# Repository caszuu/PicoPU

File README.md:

# PicoPU

A mecha project focused on building a very simple open-source General Purpose Graphics Processing Unit (GPGPU) using the amazing `rp2350` MCUs as compute cores. The project it self is made of multiple parts: the software drivers, the GPU firmware and the hardware PCB itself.

The project is currently very WIP, more is to come.

Monorepo subprojects:
- `core-firmware/` - PicoPU firmware
	- `common/` - shared firmware utilities
 	- `usbd/` - a protocol generic `tinyusb` device driver
  	- `dvid/` - a simple hstx-based dvi driver
  	- `gcs/` - an arch agnostic software renderer
	- `arch/` - device architecture specific source files
		- `mockbird/` - RPi Pico 2 (mocking bird) arch firmware
- `pdrv/` - a user-space host-side driver written in go
	- `bench/` - an example application using directly `pdrv` apis
- `boards/` - Board design files
	- `images` - used images, #TODO add images of boards
	- `broker` - EasyEDA Std. file for the Broker/Motherboard
	- `shader` - EasyEDA Std. file for the smaller Shader boards
	- `just-V2` - EasyEDA Std. file for the V2 board
	- `pcie` - KiCad project with the "V3" pcie edition

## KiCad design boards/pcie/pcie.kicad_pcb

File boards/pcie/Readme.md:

pcie template from here <3 - https://github.com/lucanastasio/PCIexpress-KiCad/

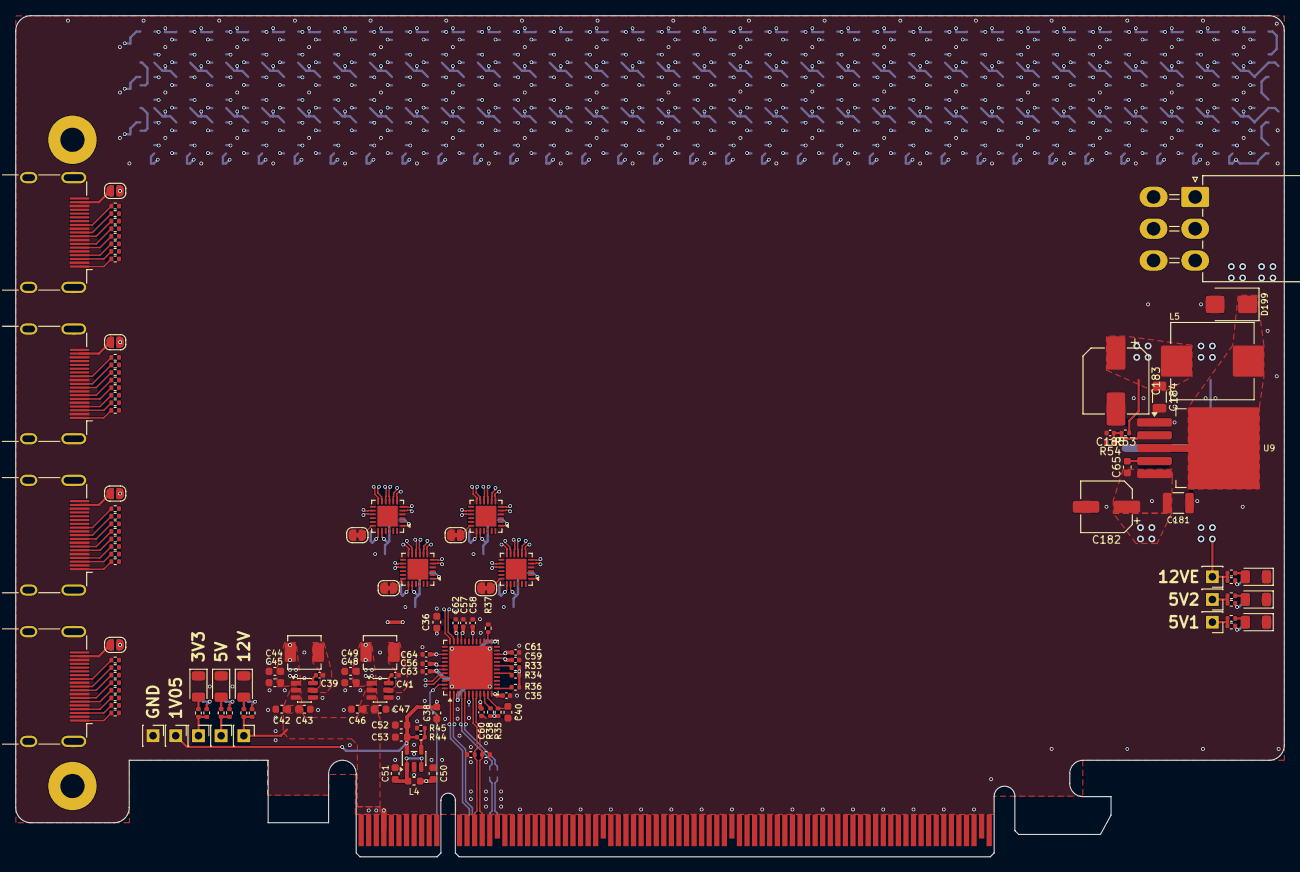
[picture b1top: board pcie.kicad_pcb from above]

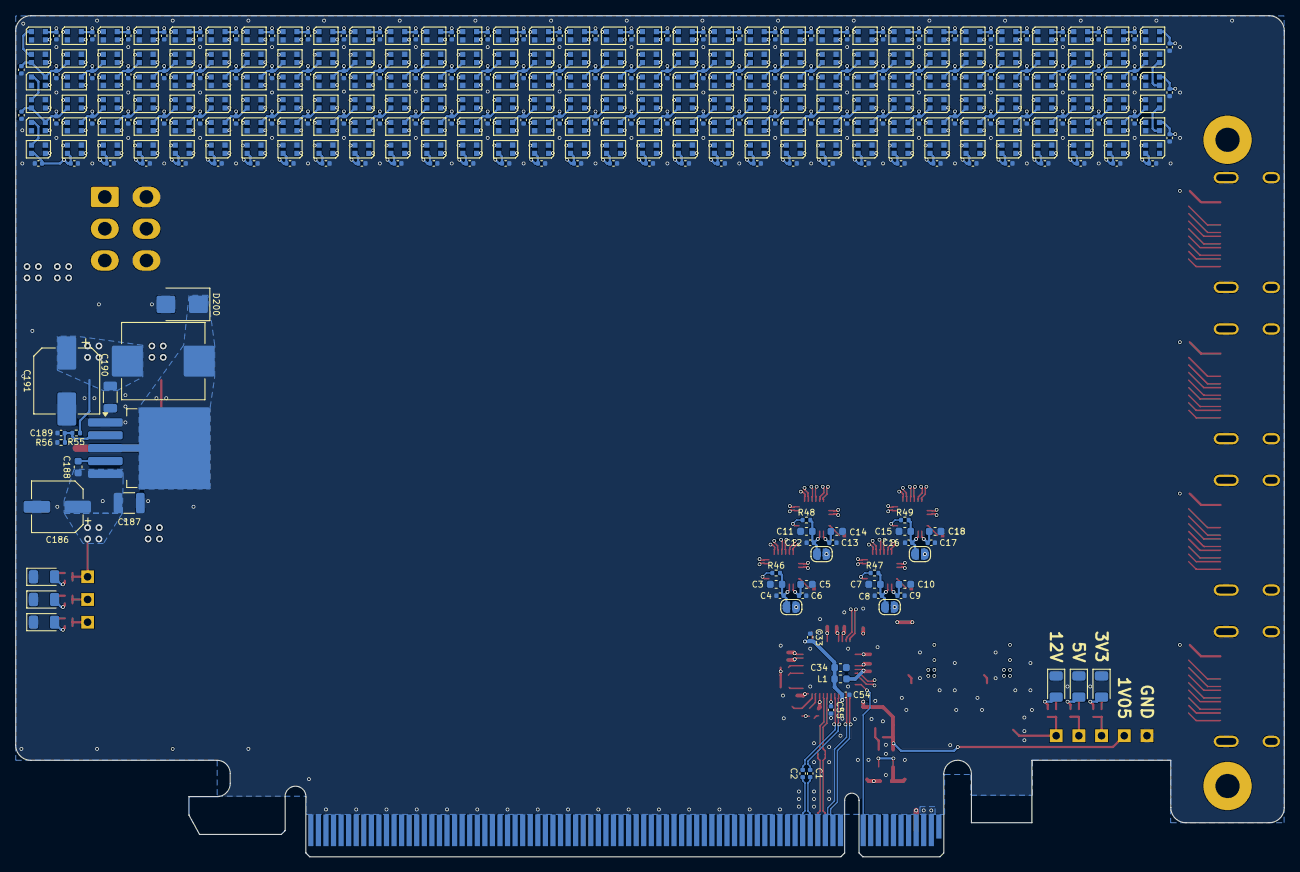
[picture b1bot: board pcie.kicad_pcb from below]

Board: 4 copper layers, 167.6 x 111.2 mm, 504 parts (370 on the bottom side), 295 nets.

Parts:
C1, C2, C4, C6, C8, C9, C12, C13, C16, C17, C19, C20, C21, C22, C23, C24, C25, C26, C27, C28, C29, C30, C31, C32, C33, C35, C37, C39, C41, C54, C55, C56, C57, C58, C59, C60, C61, C62, C63, C64, C66, C67, C68, C69, C70, C71, C72, C73, C74, C75, C76, C77, C78, C79, C80, C81, C82, C83, C84, C85, C86, C87, C88, C89, C90, C91, C92, C93, C94, C95, C96, C97, C98, C99, C100, C101, C102, C103, C104, C105, C106, C107, C108, C109, C110, C111, C112, C113, C114, C115, C116, C117, C118, C119, C120, C121, C122, C123, C124, C125, C126, C127, C128, C129, C130, C131, C132, C133, C134, C135, C136, C137, C138, C139, C140, C141, C142, C143, C144, C145, C146, C147, C148, C149, C150, C151, C152, C153, C154, C155, C156, C157, C158, C159, C160, C161, C162, C163, C164, C165, C166, C167, C168, C169, C170, C171, C172, C173, C174, C175, C176, C177, C178, C179, C180: 100nF; C_0402_1005Metric
C3, C5, C7, C10, C11, C14, C15, C18, C34, C36, C38, C40, C65, C188: 1uF; C_0603_1608Metric
C42, C46, C50, C51, C52: 10uF; C_0603_1608Metric
C43, C44, C45, C47, C48, C49, C53: 22uF; C_0603_1608Metric
C181, C187: 22uF@25V; C_1210_3225Metric
C182, C186: 220uF@25V; CP_Elec_6.3x7.7
C183, C191: 470uF@16V; CP_Elec_8x10.5
C184, C190: 22uF@10V; C_1206_3216Metric
C185, C189: 33nF; C_0402_1005Metric
D1, D4: 12V; LED_1206_3216Metric
D2, D5: 5V; LED_1206_3216Metric
D3, D6: 3V3; LED_1206_3216Metric
D7, D8, D9, D10, D11, D12, D13, D14, D15, D16, D17, D18, D19, D20, D21, D22, D23, D24, D25, D26, D27, D28, D29, D30, D31, D32, D33, D34, D35, D36, D37, D38, D39, D40, D41, D42, D43, D44, D45, D46, D47, D48, D49, D50, D51, D52, D53, D54, D55, D56, D57, D58, D59, D60, D61, D62, D63, D64, D65, D66, D67, D68, D69, D70, D71, D72, D73, D74, D75, D76, D77, D78, D79, D80, D81, D82, D83, D84, D85, D86, D87, D88, D89, D90, D91, D92, D93, D94, D95, D96, D97, D98, D99, D100, D101, D102, D103, D104, D105, D106, D107, D108, D109, D110, D111, D112, D113, D114, D115, D116, D117, D118, D119, D120, D121, D122, D123, D124, D125, D126, D127, D128, D129, D130, D131, D132, D133, D134, D135, D136, D137, D138, D139, D140, D141, D142, D143, D144, D145, D146, D147, D148, D149, D150, D151, D152, D153, D154, D155, D156, D157, D158, D159, D160, D161, D162, D163, D164, D165, D166, D167, D168, D169, D170, D171, D172, D173, D174, D175, D176, D177, D178, D179, D180, D181, D182, D183, D184, D185, D186, D187, D188, D189, D190, D191, D192, D193, D194, D195, D196, D197, D198: LED_45deg; LED_WS2812B-2020_PLCC4_2.0x2.0mm
D199, D200: SS1045-SMB; D_SMB
D201, D202: 12VE; LED_1206_3216Metric
D203, D204: LED_5V1; LED_1206_3216Metric
D205, D206: LED_5V2; LED_1206_3216Metric
H1, H2: MountingHole; MountingHole_3.2mm_M3_Pad
J1: PCIexpress_bracket; PCIexpress_bracket_full
J2: PCIexpress_x16
J3, J13: 12V; PinHeader_1x01_P2.54mm_Vertical
J4, J14, J15: 5V; PinHeader_1x01_P2.54mm_Vertical
J5: 3V3; PinHeader_1x01_P2.54mm_Vertical
J6: 1V0; PinHeader_1x01_P2.54mm_Vertical
J7: GND; PinHeader_1x01_P2.54mm_Vertical
J8, J9, J10, J11: HDMI_A; HDMI_A_Molex_208658-1001_Horizontal
J12: Conn_02x03_Odd_Even; Molex_Mini-Fit_Jr_5569-06A1_2x03_P4.20mm_Horizontal
JP1, JP2, JP3, JP4, JP5, JP8, JP10, JP12: SolderJumper_2_Open; SolderJumper-2_P1.3mm_Open_RoundedPad1.0x1.5mm
JP6, JP7, JP9, JP11: SolderJumper_2_Bridged; SolderJumper-2_P1.3mm_Bridged_RoundedPad1.0x1.5mm
L1, L4: 600Ω@100MHz; L_0603_1608Metric
L2: 4.7uH; L_APV_APH0420
L3: 3.3uH; L_APV_APH0420
L5, L6: 33uH; L_APV_APH1050
R1, R2: 49R9; R_0402_1005Metric
R3, R50, R54, R56, R57, R58: 1k; R_0402_1005Metric
R4, R6, R7, R8, R9, R10, R11, R12, R13, R14, R15, R16, R17, R18, R19, R20, R21, R22, R23, R24, R25, R26, R27, R28, R29, R30, R31, R32, R39, R40, R41, R42, R43, R51, R59, R60, R61, R62: 270; R_0402_1005Metric
R5, R52: 100; R_0402_1005Metric
R33, R34, R36, R38, R45, R46, R47, R48, R49: 10k; R_0402_1005Metric
R35: 100k; R_0402_1005Metric
R37: 12k 1%; R_0402_1005Metric
R44: 9k1; R_0402_1005Metric
R53, R55: 3k; R_0402_1005Metric
U1: AP63203WU; TSOT-23-6
U2: UPD720202K8-701-BAA; QFN-48-1EP_7x7mm_P0.5mm_EP5.7x5.7mm
U3: AP63205WU; TSOT-23-6
U4: TLV75801PDBVR; SOT-23-5
U5, U6, U7, U8: CH334F; QFN-24-1EP_4x4mm_P0.5mm_EP2.7x2.7mm
U9, U10: XL4015; TO-263-5_TabPin3

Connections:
+1V0: C38.1, C52.1, C53.1, C55.1, C56.1, C57.1, C58.1, C59.1, C60.1, C64.1, J6.1 (Pin_1_1), R44.1, U2.6 (VDD10), U2.9 (VDD10), U2.21 (VDD10), U2.30 (VDD10), U2.33 (VDD10), U2.39 (VDD10), U2.42 (VDD10), U4.5 (OUT)
+3V3: C35.1, C36.1, C48.1, C49.1, C50.2, C61.1, C62.1, C63.1, J5.1 (Pin_1_1), JP5.2 (B), JP8.2 (B), JP10.2 (B), JP12.2 (B), L1.1, L3.2, L4.1, R5.1, R33.2, R34.2, R35.1, R36.2, R38.2, R52.1, U1.1 (FB), U2.12 (VDD33), U2.22 (VDD33), U2.34 (VDD33), U2.43 (VDD33)
+5V: C5.1, C6.1, C9.1, C10.1, C13.1, C14.1, C17.1, C18.1, C44.1, C45.1, J4.1 (Pin_1_1), JP1.2 (B), JP2.2 (B), JP3.2 (B), JP4.2 (B), L2.2, R4.1, R51.1, U3.1 (FB), U5.19 (V5), U6.19 (V5), U7.19 (V5), U8.19 (V5)
+12V: C42.1, C43.1, C46.1, C47.1, J2.A2 (+12V), J2.A3 (+12V), J2.B1 (+12V), J2.B2 (+12V), J2.B3 (+12V), J3.1 (Pin_1_1), R3.1, R50.1, U1.2 (EN), U1.3 (IN), U3.2 (EN), U3.3 (IN)
+12VE: C65.1, C181.1, C182.1, C186.1, C187.1, C188.1, J12.1, J12.3, J13.1 (Pin_1_1), R57.1, R58.1, U9.5 (VIN), U10.5 (VIN)
/Hubs/UDUSB1_DN: U5.11 (DM1-), U7.14 (DMU-)
/Hubs/UDUSB1_DP: U5.12 (DP1+), U7.15 (DPU+)
/Hubs/UDUSB2_DN: U6.11 (DM1-), U8.14 (DMU-)
/Hubs/UDUSB2_DP: U6.12 (DP1+), U8.15 (DPU+)
/Hubs/UUSB1_DN: U2.36 (U2DM1), U5.14 (DMU-)
/Hubs/UUSB1_DP: U2.35 (U2DP1), U5.15 (DPU+)
/Hubs/UUSB2_DN: U2.45 (U2DM2), U6.14 (DMU-)
/Hubs/UUSB2_DP: U2.44 (U2DP2), U6.15 (DPU+)
/PER0_N: C2.2, U2.5 (PETXN)
/PER0_P: C1.1, U2.4 (PETXP)
/PET0_N: J2.B15 (PETn0), R1.1, U2.8 (PERXN)
/PET0_P: J2.B14 (PETp0), R2.1, U2.7 (PERXP)
/REFCLK+: J2.A13 (REFCLK+), U2.1 (PECLKP)
/REFCLK-: J2.A14 (REFCLK-), U2.2 (PECLKN)
/_PER0_N: C2.1, J2.A17 (PERn0)
/_PER0_P: C1.2, J2.A16 (PERp0)
/~PERST: J2.A11 (~PERST), U2.47 (~PERST)
GND: C3.2, C4.2, C5.2, C6.2, C7.2, C8.2, C9.2, C10.2, C11.2, C12.2, C13.2, C14.2, C15.2, C16.2, C17.2, C18.2, C19.2, C20.2, C21.2, C22.2, C23.2, C24.2, C25.2, C26.2, C27.2, C28.2, C29.2, C30.2, C31.2, C32.2, C33.1, C34.1, C35.2, C36.2, C37.2, C38.2, C40.2, C42.2, C43.2, C44.2, C45.2, C46.2, C47.2, C48.2, C49.2, C50.1, C51.1, C52.2, C53.2, C54.1, C55.2, C56.2, C57.2, C58.2, C59.2, C60.2, C61.2, C62.2, C63.2, C64.2, C66.2, C67.2, C68.2, C69.2, C70.2, C71.2, C72.2, C73.2, C74.2, C75.2, C76.2, C77.2, C78.2, C79.2, C80.2, C81.2, C82.2, C83.2, C84.2, C85.2, C86.2, C87.2, C88.2, C89.2, C90.2, C91.2, C92.2, C93.2, C94.2, C95.2, C96.2, C97.2, C98.2, C99.2, C100.2, C101.2, C102.2, C103.2, C104.2, C105.2, C106.2, C107.2, C108.2, C109.2, C110.2, C111.2, C112.2, C113.2, C114.2, C115.2, C116.2, C117.2, C118.2, C119.2, C120.2, C121.2, C122.2, C123.2, C124.2, C125.2, C126.2, C127.2, C128.2, C129.2, C130.2, C131.2, C132.2, C133.2, C134.2, C135.2, C136.2, C137.2, C138.2, C139.2, C140.2, C141.2, C142.2, C143.2, C144.2, C145.2, C146.2, C147.2, C148.2, C149.2, C150.2, C151.2, C152.2, C153.2, C154.2, C155.2, C156.2, C157.2, C158.2, C159.2, C160.2, C161.2, C162.2, C163.2, C164.2, C165.2, C166.2, C167.2, C168.2, C169.2, C170.2, C171.2, C172.2, C173.2, C174.2, C175.2, C176.2, C177.2, C178.2, C179.2, C180.2, C181.2, C182.2, C183.2, C184.2, C185.2, C186.2, C187.2, C189.2, C190.2, C191.2, D1.1 (K), D2.1 (K), D3.1 (K), D4.1 (K), D5.1 (K), D6.1 (K), D7.2 (VSS), D8.2 (VSS), D9.2 (VSS), D10.2 (VSS), D11.2 (VSS), D12.2 (VSS), D13.2 (VSS), D14.2 (VSS), D15.2 (VSS), D16.2 (VSS), D17.2 (VSS), D18.2 (VSS), D19.2 (VSS), D20.2 (VSS), D21.2 (VSS), D22.2 (VSS), D23.2 (VSS), D24.2 (VSS), D25.2 (VSS), D26.2 (VSS), D27.2 (VSS), D28.2 (VSS), D29.2 (VSS), D30.2 (VSS), D31.2 (VSS), D32.2 (VSS), D33.2 (VSS), D34.2 (VSS), D35.2 (VSS), D36.2 (VSS), D37.2 (VSS), D38.2 (VSS), D39.2 (VSS), D40.2 (VSS), D41.2 (VSS), D42.2 (VSS), D43.2 (VSS), D44.2 (VSS), D45.2 (VSS), D46.2 (VSS), D47.2 (VSS), D48.2 (VSS), D49.2 (VSS), D50.2 (VSS), D51.2 (VSS), D52.2 (VSS), D53.2 (VSS), D54.2 (VSS), D55.2 (VSS), D56.2 (VSS), D57.2 (VSS), D58.2 (VSS), D59.2 (VSS), D60.2 (VSS), D61.2 (VSS), D62.2 (VSS), D63.2 (VSS), D64.2 (VSS), D65.2 (VSS), D66.2 (VSS), D67.2 (VSS), D68.2 (VSS), D69.2 (VSS), D70.2 (VSS), D71.2 (VSS), D72.2 (VSS), D73.2 (VSS), D74.2 (VSS), D75.2 (VSS), D76.2 (VSS), D77.2 (VSS), D78.2 (VSS), D79.2 (VSS), D80.2 (VSS), D81.2 (VSS), D82.2 (VSS), D83.2 (VSS), D84.2 (VSS), D85.2 (VSS), D86.2 (VSS), D87.2 (VSS), D88.2 (VSS), D89.2 (VSS), D90.2 (VSS), D91.2 (VSS), D92.2 (VSS), D93.2 (VSS), D94.2 (VSS), D95.2 (VSS), D96.2 (VSS), D97.2 (VSS), D98.2 (VSS), D99.2 (VSS), D100.2 (VSS), D101.2 (VSS), D102.2 (VSS), D103.2 (VSS), D104.2 (VSS), D105.2 (VSS), D106.2 (VSS), D107.2 (VSS), D108.2 (VSS), D109.2 (VSS), D110.2 (VSS), D111.2 (VSS), D112.2 (VSS), D113.2 (VSS), D114.2 (VSS), D115.2 (VSS), D116.2 (VSS), D117.2 (VSS), D118.2 (VSS), D119.2 (VSS), D120.2 (VSS), D121.2 (VSS), D122.2 (VSS), D123.2 (VSS), D124.2 (VSS), D125.2 (VSS), D126.2 (VSS), D127.2 (VSS), D128.2 (VSS), D129.2 (VSS), D130.2 (VSS), D131.2 (VSS), D132.2 (VSS), D133.2 (VSS), D134.2 (VSS), D135.2 (VSS), D136.2 (VSS), D137.2 (VSS), D138.2 (VSS), D139.2 (VSS), D140.2 (VSS), D141.2 (VSS), D142.2 (VSS), D143.2 (VSS), D144.2 (VSS), D145.2 (VSS), D146.2 (VSS), D147.2 (VSS), D148.2 (VSS), D149.2 (VSS), D150.2 (VSS), D151.2 (VSS), D152.2 (VSS), D153.2 (VSS), D154.2 (VSS), D155.2 (VSS), D156.2 (VSS), D157.2 (VSS), D158.2 (VSS), D159.2 (VSS), D160.2 (VSS), D161.2 (VSS), D162.2 (VSS), D163.2 (VSS), D164.2 (VSS), D165.2 (VSS), D166.2 (VSS), D167.2 (VSS), D168.2 (VSS), D169.2 (VSS), D170.2 (VSS), D171.2 (VSS), D172.2 (VSS), D173.2 (VSS), D174.2 (VSS), D175.2 (VSS), D176.2 (VSS), D177.2 (VSS), D178.2 (VSS), D179.2 (VSS), D180.2 (VSS), D181.2 (VSS), D182.2 (VSS), D183.2 (VSS), D184.2 (VSS), D185.2 (VSS), D186.2 (VSS), D187.2 (VSS), D188.2 (VSS), D189.2 (VSS), D190.2 (VSS), D191.2 (VSS), D192.2 (VSS), D193.2 (VSS), D194.2 (VSS), D195.2 (VSS), D196.2 (VSS), D197.2 (VSS), D198.2 (VSS), D199.2 (A), D200.2 (A), D201.1 (K), D202.1 (K), D203.1 (K), D204.1 (K), D205.1 (K), D206.1 (K), J2.A4 (GND), J2.A12 (GND), J2.A15 (GND), J2.A18 (GND), J2.A20 (GND), J2.A23 (GND), J2.A24 (GND), J2.A27 (GND), J2.A28 (GND), J2.A31 (GND), J2.A34 (GND), J2.A37 (GND), J2.A38 (GND), J2.A41 (GND), J2.A42 (GND), J2.A45 (GND), J2.A46 (GND), J2.A49 (GND), J2.A51 (GND), J2.A54 (GND), J2.A55 (GND), J2.A58 (GND), J2.A59 (GND), J2.A62 (GND), J2.A63 (GND), J2.A66 (GND), J2.A67 (GND), J2.A70 (GND), J2.A71 (GND), J2.A74 (GND), J2.A75 (GND), J2.A78 (GND), J2.A79 (GND), J2.A82 (GND), J2.B4 (GND), J2.B7 (GND), J2.B13 (GND), J2.B16 (GND), J2.B17 (~PRSNT2), J2.B18 (GND), J2.B21 (GND), J2.B22 (GND), J2.B25 (GND), J2.B26 (GND), J2.B29 (GND), J2.B32 (GND), J2.B35 (GND), J2.B36 (GND), J2.B39 (GND), J2.B40 (GND), J2.B43 (GND), J2.B44 (GND), J2.B47 (GND), J2.B49 (GND), J2.B52 (GND), J2.B53 (GND), J2.B56 (GND), J2.B57 (GND), J2.B60 (GND), J2.B61 (GND), J2.B64 (GND), J2.B65 (GND), J2.B68 (GND), J2.B69 (GND), J2.B72 (GND), J2.B73 (GND), J2.B76 (GND), J2.B77 (GND), J2.B80 (GND), J7.1 (Pin_1_1), J8.2 (D2S), J8.5 (D1S), J8.8 (D0S), J8.11 (CKS), J8.17 (GND), J8.SH, J9.2 (D2S), J9.5 (D1S), J9.8 (D0S), J9.11 (CKS), J9.17 (GND), J9.SH, J10.2 (D2S), J10.5 (D1S), J10.8 (D0S), J10.11 (CKS), J10.17 (GND), J10.SH, J11.2 (D2S), J11.5 (D1S), J11.8 (D0S), J11.11 (CKS), J11.17 (GND), J11.SH, J12.4, J12.6, JP6.1 (A), JP7.1 (A), JP9.1 (A), JP11.1 (A), R1.2, R2.2, R37.2, R45.2, R54.2, R56.2, U1.4 (GND), U2.27 (GND), U2.49 (GND), U3.4 (GND), U4.2 (GND), U5.4 (XI), U5.25 (GND), U6.4 (XI), U6.25 (GND), U7.4 (XI), U7.25 (GND), U8.4 (XI), U8.25 (GND), U9.1 (GND), U10.1 (GND)
LED_5V1: C19.1, C20.1, C21.1, C22.1, C27.1, C28.1, C29.1, C30.1, C31.1, C32.1, C37.1, C66.1, C67.1, C68.1, C69.1, C70.1, C71.1, C72.1, C73.1, C74.1, C75.1, C76.1, C77.1, C78.1, C79.1, C80.1, C81.1, C82.1, C83.1, C84.1, C85.1, C86.1, C87.1, C149.1, C150.1, C151.1, C152.1, C153.1, C154.1, C155.1, C156.1, C157.1, C158.1, C159.1, C160.1, C161.1, C162.1, C163.1, C164.1, C165.1, C166.1, C167.1, C168.1, C169.1, C170.1, C171.1, C172.1, C173.1, C174.1, C175.1, C176.1, C177.1, C178.1, C179.1, C180.1, C190.1, C191.1, D7.4 (VDD), D8.4 (VDD), D9.4 (VDD), D10.4 (VDD), D11.4 (VDD), D12.4 (VDD), D13.4 (VDD), D14.4 (VDD), D15.4 (VDD), D16.4 (VDD), D17.4 (VDD), D18.4 (VDD), D19.4 (VDD), D20.4 (VDD), D21.4 (VDD), D22.4 (VDD), D23.4 (VDD), D24.4 (VDD), D25.4 (VDD), D26.4 (VDD), D27.4 (VDD), D28.4 (VDD), D29.4 (VDD), D30.4 (VDD), D31.4 (VDD), D32.4 (VDD), D33.4 (VDD), D34.4 (VDD), D35.4 (VDD), D36.4 (VDD), D37.4 (VDD), D38.4 (VDD), D39.4 (VDD), D40.4 (VDD), D41.4 (VDD), D42.4 (VDD), D43.4 (VDD), D44.4 (VDD), D45.4 (VDD), D46.4 (VDD), D47.4 (VDD), D48.4 (VDD), D49.4 (VDD), D50.4 (VDD), D51.4 (VDD), D52.4 (VDD), D53.4 (VDD), D54.4 (VDD), D55.4 (VDD), D56.4 (VDD), D57.4 (VDD), D58.4 (VDD), D59.4 (VDD), D60.4 (VDD), D61.4 (VDD), D62.4 (VDD), D63.4 (VDD), D64.4 (VDD), D65.4 (VDD), D66.4 (VDD), D67.4 (VDD), D68.4 (VDD), D69.4 (VDD), D70.4 (VDD), D71.4 (VDD), D72.4 (VDD), D73.4 (VDD), D74.4 (VDD), D75.4 (VDD), D76.4 (VDD), D77.4 (VDD), D78.4 (VDD), D79.4 (VDD), D80.4 (VDD), D81.4 (VDD), D82.4 (VDD), D83.4 (VDD), D84.4 (VDD), D85.4 (VDD), D86.4 (VDD), D87.4 (VDD), D88.4 (VDD), D89.4 (VDD), D90.4 (VDD), D91.4 (VDD), D92.4 (VDD), D93.4 (VDD), D94.4 (VDD), D95.4 (VDD), D96.4 (VDD), D97.4 (VDD), D98.4 (VDD), D99.4 (VDD), D100.4 (VDD), D101.4 (VDD), D102.4 (VDD), J14.1 (Pin_1_1), L6.2, R55.1, R59.1, R60.1
LED_5V2: C23.1, C24.1, C25.1, C26.1, C88.1, C89.1, C90.1, C91.1, C92.1, C93.1, C94.1, C95.1, C96.1, C97.1, C98.1, C99.1, C100.1, C101.1, C102.1, C103.1, C104.1, C105.1, C106.1, C107.1, C108.1, C109.1, C110.1, C111.1, C112.1, C113.1, C114.1, C115.1, C116.1, C117.1, C118.1, C119.1, C120.1, C121.1, C122.1, C123.1, C124.1, C125.1, C126.1, C127.1, C128.1, C129.1, C130.1, C131.1, C132.1, C133.1, C134.1, C135.1, C136.1, C137.1, C138.1, C139.1, C140.1, C141.1, C142.1, C143.1, C144.1, C145.1, C146.1, C147.1, C148.1, C183.1, C184.1, D103.4 (VDD), D104.4 (VDD), D105.4 (VDD), D106.4 (VDD), D107.4 (VDD), D108.4 (VDD), D109.4 (VDD), D110.4 (VDD), D111.4 (VDD), D112.4 (VDD), D113.4 (VDD), D114.4 (VDD), D115.4 (VDD), D116.4 (VDD), D117.4 (VDD), D118.4 (VDD), D119.4 (VDD), D120.4 (VDD), D121.4 (VDD), D122.4 (VDD), D123.4 (VDD), D124.4 (VDD), D125.4 (VDD), D126.4 (VDD), D127.4 (VDD), D128.4 (VDD), D129.4 (VDD), D130.4 (VDD), D131.4 (VDD), D132.4 (VDD), D133.4 (VDD), D134.4 (VDD), D135.4 (VDD), D136.4 (VDD), D137.4 (VDD), D138.4 (VDD), D139.4 (VDD), D140.4 (VDD), D141.4 (VDD), D142.4 (VDD), D143.4 (VDD), D144.4 (VDD), D145.4 (VDD), D146.4 (VDD), D147.4 (VDD), D148.4 (VDD), D149.4 (VDD), D150.4 (VDD), D151.4 (VDD), D152.4 (VDD), D153.4 (VDD), D154.4 (VDD), D155.4 (VDD), D156.4 (VDD), D157.4 (VDD), D158.4 (VDD), D159.4 (VDD), D160.4 (VDD), D161.4 (VDD), D162.4 (VDD), D163.4 (VDD), D164.4 (VDD), D165.4 (VDD), D166.4 (VDD), D167.4 (VDD), D168.4 (VDD), D169.4 (VDD), D170.4 (VDD), D171.4 (VDD), D172.4 (VDD), D173.4 (VDD), D174.4 (VDD), D175.4 (VDD), D176.4 (VDD), D177.4 (VDD), D178.4 (VDD), D179.4 (VDD), D180.4 (VDD), D181.4 (VDD), D182.4 (VDD), D183.4 (VDD), D184.4 (VDD), D185.4 (VDD), D186.4 (VDD), D187.4 (VDD), D188.4 (VDD), D189.4 (VDD), D190.4 (VDD), D191.4 (VDD), D192.4 (VDD), D193.4 (VDD), D194.4 (VDD), D195.4 (VDD), D196.4 (VDD), D197.4 (VDD), D198.4 (VDD), J15.1 (Pin_1_1), L5.2, R53.1, R61.1, R62.1
unnamed: C33.2, C34.2, C54.2, L1.2, U2.3 (AVDD33), U2.25 (AVDD33)
unnamed: D1.2 (A), R3.2
unnamed: D2.2 (A), R4.2
unnamed: D3.2 (A), R5.2
unnamed: D4.2 (A), R50.2
unnamed: D5.2 (A), R51.2
unnamed: D6.2 (A), R52.2
unnamed: D7.1 (DOUT), D8.3 (DIN)
unnamed: D8.1 (DOUT), D9.3 (DIN)
unnamed: D9.1 (DOUT), D10.3 (DIN)
unnamed: D10.1 (DOUT), D11.3 (DIN)
unnamed: D11.1 (DOUT), D12.3 (DIN)
unnamed: D12.1 (DOUT), D13.3 (DIN)
unnamed: D13.1 (DOUT), D14.3 (DIN)
unnamed: D14.1 (DOUT), D15.3 (DIN)
unnamed: D15.1 (DOUT), D16.3 (DIN)
unnamed: D16.1 (DOUT), D17.3 (DIN)
unnamed: D17.1 (DOUT), D18.3 (DIN)
unnamed: D18.1 (DOUT), D19.3 (DIN)
unnamed: D19.1 (DOUT), D20.3 (DIN)
unnamed: D20.1 (DOUT), D21.3 (DIN)
unnamed: D21.1 (DOUT), D22.3 (DIN)
unnamed: D22.1 (DOUT), D23.3 (DIN)
unnamed: D23.1 (DOUT), D24.3 (DIN)
unnamed: D24.1 (DOUT), D25.3 (DIN)
unnamed: D25.1 (DOUT), D26.3 (DIN)
unnamed: D26.1 (DOUT), D27.3 (DIN)
unnamed: D27.1 (DOUT), D28.3 (DIN)
unnamed: D28.1 (DOUT), D29.3 (DIN)
unnamed: D29.1 (DOUT), D30.3 (DIN)
unnamed: D30.1 (DOUT), D31.3 (DIN)
unnamed: D31.1 (DOUT), D32.3 (DIN)
unnamed: D32.1 (DOUT), D33.3 (DIN)
unnamed: D33.1 (DOUT), D34.3 (DIN)
unnamed: D34.1 (DOUT), D35.3 (DIN)
unnamed: D35.1 (DOUT), D36.3 (DIN)
unnamed: D36.1 (DOUT), D37.3 (DIN)
unnamed: D37.1 (DOUT), D38.3 (DIN)
unnamed: D38.1 (DOUT), D39.3 (DIN)
unnamed: D39.1 (DOUT), D40.3 (DIN)
unnamed: D40.1 (DOUT), D41.3 (DIN)
unnamed: D41.1 (DOUT), D42.3 (DIN)
unnamed: D42.1 (DOUT), D43.3 (DIN)
unnamed: D43.1 (DOUT), D44.3 (DIN)
unnamed: D44.1 (DOUT), D45.3 (DIN)
unnamed: D45.1 (DOUT), D46.3 (DIN)
unnamed: D46.1 (DOUT), D47.3 (DIN)
unnamed: D47.1 (DOUT), D48.3 (DIN)
unnamed: D48.1 (DOUT), D49.3 (DIN)
unnamed: D49.1 (DOUT), D50.3 (DIN)
unnamed: D50.1 (DOUT), D51.3 (DIN)
unnamed: D51.1 (DOUT), D52.3 (DIN)
unnamed: D52.1 (DOUT), D53.3 (DIN)
unnamed: D53.1 (DOUT), D54.3 (DIN)
unnamed: D54.1 (DOUT), D55.3 (DIN)
unnamed: D55.1 (DOUT), D56.3 (DIN)
unnamed: D56.1 (DOUT), D57.3 (DIN)
unnamed: D57.1 (DOUT), D58.3 (DIN)
unnamed: D58.1 (DOUT), D59.3 (DIN)
unnamed: D59.1 (DOUT), D60.3 (DIN)
unnamed: D60.1 (DOUT), D61.3 (DIN)
unnamed: D61.1 (DOUT), D62.3 (DIN)
unnamed: D62.1 (DOUT), D63.3 (DIN)
unnamed: D63.1 (DOUT), D64.3 (DIN)
unnamed: D64.1 (DOUT), D65.3 (DIN)
unnamed: D65.1 (DOUT), D66.3 (DIN)
unnamed: D66.1 (DOUT), D67.3 (DIN)
unnamed: D67.1 (DOUT), D68.3 (DIN)
unnamed: D68.1 (DOUT), D69.3 (DIN)
unnamed: D69.1 (DOUT), D70.3 (DIN)
unnamed: D70.1 (DOUT), D71.3 (DIN)
unnamed: D71.1 (DOUT), D72.3 (DIN)
unnamed: D72.1 (DOUT), D73.3 (DIN)
unnamed: D73.1 (DOUT), D74.3 (DIN)
unnamed: D74.1 (DOUT), D75.3 (DIN)
unnamed: D75.1 (DOUT), D76.3 (DIN)
unnamed: D76.1 (DOUT), D77.3 (DIN)
unnamed: D77.1 (DOUT), D78.3 (DIN)
unnamed: D78.1 (DOUT), D79.3 (DIN)
unnamed: D79.1 (DOUT), D80.3 (DIN)
unnamed: D80.1 (DOUT), D81.3 (DIN)
unnamed: D81.1 (DOUT), D82.3 (DIN)
unnamed: D82.1 (DOUT), D83.3 (DIN)
unnamed: D83.1 (DOUT), D84.3 (DIN)
unnamed: D84.1 (DOUT), D85.3 (DIN)
unnamed: D85.1 (DOUT), D86.3 (DIN)
unnamed: D86.1 (DOUT), D87.3 (DIN)
unnamed: D87.1 (DOUT), D88.3 (DIN)
unnamed: D88.1 (DOUT), D89.3 (DIN)
unnamed: D89.1 (DOUT), D90.3 (DIN)
unnamed: D90.1 (DOUT), D91.3 (DIN)
unnamed: D91.1 (DOUT), D92.3 (DIN)
unnamed: D92.1 (DOUT), D93.3 (DIN)
unnamed: D93.1 (DOUT), D94.3 (DIN)
unnamed: D94.1 (DOUT), D95.3 (DIN)
unnamed: D95.1 (DOUT), D96.3 (DIN)
unnamed: D96.1 (DOUT), D97.3 (DIN)
unnamed: D97.1 (DOUT), D98.3 (DIN)
unnamed: D98.1 (DOUT), D99.3 (DIN)
unnamed: D99.1 (DOUT), D100.3 (DIN)
unnamed: D100.1 (DOUT), D101.3 (DIN)
unnamed: D101.1 (DOUT), D102.3 (DIN)
unnamed: D102.1 (DOUT), D103.3 (DIN)
unnamed: D103.1 (DOUT), D104.3 (DIN)
unnamed: D104.1 (DOUT), D105.3 (DIN)
unnamed: D105.1 (DOUT), D106.3 (DIN)
unnamed: D106.1 (DOUT), D107.3 (DIN)
unnamed: D107.1 (DOUT), D108.3 (DIN)
unnamed: D108.1 (DOUT), D109.3 (DIN)
unnamed: D109.1 (DOUT), D110.3 (DIN)
unnamed: D110.1 (DOUT), D111.3 (DIN)
unnamed: D111.1 (DOUT), D112.3 (DIN)
unnamed: D112.1 (DOUT), D113.3 (DIN)
unnamed: D113.1 (DOUT), D114.3 (DIN)
unnamed: D114.1 (DOUT), D115.3 (DIN)
unnamed: D115.1 (DOUT), D116.3 (DIN)
unnamed: D116.1 (DOUT), D117.3 (DIN)
unnamed: D117.1 (DOUT), D118.3 (DIN)
unnamed: D118.1 (DOUT), D119.3 (DIN)
unnamed: D119.1 (DOUT), D120.3 (DIN)
unnamed: D120.1 (DOUT), D121.3 (DIN)
unnamed: D121.1 (DOUT), D122.3 (DIN)
unnamed: D122.1 (DOUT), D123.3 (DIN)
unnamed: D123.1 (DOUT), D124.3 (DIN)
unnamed: D124.1 (DOUT), D125.3 (DIN)
unnamed: D125.1 (DOUT), D126.3 (DIN)
unnamed: D126.1 (DOUT), D127.3 (DIN)
unnamed: D127.1 (DOUT), D128.3 (DIN)
unnamed: D128.1 (DOUT), D129.3 (DIN)
unnamed: D129.1 (DOUT), D130.3 (DIN)
unnamed: D130.1 (DOUT), D131.3 (DIN)
unnamed: D131.1 (DOUT), D132.3 (DIN)
unnamed: D132.1 (DOUT), D133.3 (DIN)
unnamed: D133.1 (DOUT), D134.3 (DIN)
unnamed: D134.1 (DOUT), D135.3 (DIN)
unnamed: D135.1 (DOUT), D136.3 (DIN)
unnamed: D136.1 (DOUT), D137.3 (DIN)
unnamed: D137.1 (DOUT), D138.3 (DIN)
unnamed: D138.1 (DOUT), D139.3 (DIN)
unnamed: D139.1 (DOUT), D140.3 (DIN)
unnamed: D140.1 (DOUT), D141.3 (DIN)
unnamed: D141.1 (DOUT), D142.3 (DIN)
unnamed: D142.1 (DOUT), D143.3 (DIN)
unnamed: D143.1 (DOUT), D144.3 (DIN)
unnamed: D144.1 (DOUT), D145.3 (DIN)
unnamed: D145.1 (DOUT), D146.3 (DIN)
unnamed: D146.1 (DOUT), D147.3 (DIN)
unnamed: D147.1 (DOUT), D148.3 (DIN)
unnamed: D148.1 (DOUT), D149.3 (DIN)
unnamed: D149.1 (DOUT), D150.3 (DIN)
unnamed: D150.1 (DOUT), D151.3 (DIN)
unnamed: D151.1 (DOUT), D152.3 (DIN)
unnamed: D152.1 (DOUT), D153.3 (DIN)
unnamed: D153.1 (DOUT), D154.3 (DIN)
unnamed: D154.1 (DOUT), D155.3 (DIN)
unnamed: D155.1 (DOUT), D156.3 (DIN)
unnamed: D156.1 (DOUT), D157.3 (DIN)
unnamed: D157.1 (DOUT), D158.3 (DIN)
unnamed: D158.1 (DOUT), D159.3 (DIN)
unnamed: D159.1 (DOUT), D160.3 (DIN)
unnamed: D160.1 (DOUT), D161.3 (DIN)
unnamed: D161.1 (DOUT), D162.3 (DIN)
unnamed: D162.1 (DOUT), D163.3 (DIN)
unnamed: D163.1 (DOUT), D164.3 (DIN)
unnamed: D164.1 (DOUT), D165.3 (DIN)
unnamed: D165.1 (DOUT), D166.3 (DIN)
unnamed: D166.1 (DOUT), D167.3 (DIN)
unnamed: D167.1 (DOUT), D168.3 (DIN)
unnamed: D168.1 (DOUT), D169.3 (DIN)
unnamed: D169.1 (DOUT), D170.3 (DIN)
unnamed: D170.1 (DOUT), D171.3 (DIN)
unnamed: D171.1 (DOUT), D172.3 (DIN)
unnamed: D172.1 (DOUT), D173.3 (DIN)
unnamed: D173.1 (DOUT), D174.3 (DIN)
unnamed: D174.1 (DOUT), D175.3 (DIN)
unnamed: D175.1 (DOUT), D176.3 (DIN)
unnamed: D176.1 (DOUT), D177.3 (DIN)
unnamed: D177.1 (DOUT), D178.3 (DIN)
unnamed: D178.1 (DOUT), D179.3 (DIN)
unnamed: D179.1 (DOUT), D180.3 (DIN)
unnamed: D180.1 (DOUT), D181.3 (DIN)
unnamed: D181.1 (DOUT), D182.3 (DIN)
unnamed: D182.1 (DOUT), D183.3 (DIN)
unnamed: D183.1 (DOUT), D184.3 (DIN)
unnamed: D184.1 (DOUT), D185.3 (DIN)
unnamed: D185.1 (DOUT), D186.3 (DIN)
unnamed: D186.1 (DOUT), D187.3 (DIN)
unnamed: D187.1 (DOUT), D188.3 (DIN)
unnamed: D188.1 (DOUT), D189.3 (DIN)
unnamed: D189.1 (DOUT), D190.3 (DIN)
unnamed: D190.1 (DOUT), D191.3 (DIN)
unnamed: D191.1 (DOUT), D192.3 (DIN)
unnamed: D192.1 (DOUT), D193.3 (DIN)
unnamed: D193.1 (DOUT), D194.3 (DIN)
unnamed: D194.1 (DOUT), D195.3 (DIN)
unnamed: D195.1 (DOUT), D196.3 (DIN)
unnamed: D196.1 (DOUT), D197.3 (DIN)
unnamed: D197.1 (DOUT), D198.3 (DIN)
unnamed: D199.1 (K), L5.1, U9.3 (SW)
unnamed: D200.1 (K), L6.1, U10.3 (SW)
unnamed: D201.2 (A), R57.2
unnamed: D202.2 (A), R58.2
unnamed: D203.2 (A), R59.2
unnamed: D204.2 (A), R60.2
unnamed: D205.2 (A), R61.2
unnamed: D206.2 (A), R62.2
unnamed: J8.18 (+5V), JP1.1 (A)
unnamed: J8.12 (CKN), R13.2
unnamed: J8.10 (CKP), R12.2
unnamed: J8.9 (D0N), R11.2
unnamed: J8.7 (D0P), R10.2
unnamed: J8.6 (D1N), R9.2
unnamed: J8.4 (D1P), R8.2
unnamed: J8.3 (D2N), R7.2
unnamed: J8.1 (D2P), R6.2
unnamed: J9.18 (+5V), JP2.1 (A)
unnamed: J9.10 (CK+), R20.2
unnamed: J9.12 (CK-), R21.2
unnamed: J9.7 (D0+), R18.2
unnamed: J9.9 (D0-), R19.2
unnamed: J9.4 (D1+), R16.2
unnamed: J9.6 (D1-), R17.2
unnamed: J9.1 (D2+), R14.2
unnamed: J9.3 (D2-), R15.2
unnamed: J10.18 (+5V), JP3.1 (A)
unnamed: J10.10 (CK+), R28.2
unnamed: J10.12 (CK-), R29.2
unnamed: J10.7 (D0+), R26.2
unnamed: J10.9 (D0-), R27.2
unnamed: J10.4 (D1+), R24.2
unnamed: J10.6 (D1-), R25.2
unnamed: J10.1 (D2+), R22.2
unnamed: J10.3 (D2-), R23.2
unnamed: J11.18 (+5V), JP4.1 (A)
unnamed: J11.10 (CK+), R42.2
unnamed: J11.12 (CK-), R43.2
unnamed: J11.7 (D0+), R40.2
unnamed: J11.9 (D0-), R41.2
unnamed: J11.4 (D1+), R32.2
unnamed: J11.6 (D1-), R39.2
unnamed: J11.1 (D2+), R30.2
unnamed: J11.3 (D2-), R31.2
unnamed: C3.1, C4.1, JP5.1 (A), R46.1, U5.20 (VDD33_{LDO})
unnamed: JP6.2 (B), U5.18 (PSELF)
unnamed: JP7.2 (B), U6.18 (PSELF)
unnamed: C7.1, C8.1, JP8.1 (A), R47.1, U6.20 (VDD33_{LDO})
unnamed: JP9.2 (B), U7.18 (PSELF)
unnamed: C11.1, C12.1, JP10.1 (A), R48.1, U7.20 (VDD33_{LDO})
unnamed: JP11.2 (B), U8.18 (PSELF)
unnamed: C15.1, C16.1, JP12.1 (A), R49.1, U8.20 (VDD33_{LDO})
unnamed: C41.2, U1.6 (BST)
unnamed: C41.1, L3.1, U1.5 (SW)
unnamed: C40.1, R35.2, U2.11 (PONRSTB)
unnamed: R37.1, U2.26 (RREF)
unnamed: R36.1, U2.13 (SPISO)
unnamed: R33.1, U2.19 (~OCI1)
unnamed: R34.1, U2.17 (~OCI2)
unnamed: R38.1, U2.10 (~PECREQ)
unnamed: C39.2, U3.6 (BST)
unnamed: C39.1, L2.1, U3.5 (SW)
unnamed: C51.2, L4.2, U4.1 (IN), U4.3 (EN)
unnamed: R44.2, R45.1, U4.4 (FB)
unnamed: R46.2, U5.1 (~OVCUR)
unnamed: R47.2, U6.1 (~OVCUR)
unnamed: R48.2, U7.1 (~OVCUR)
unnamed: R49.2, U8.1 (~OVCUR)
unnamed: C185.1, R53.2, R54.1, U9.2 (FB)
unnamed: C65.2, U9.4 (VC)
unnamed: C189.1, R55.2, R56.1, U10.2 (FB)
unnamed: C188.2, U10.4 (VC)

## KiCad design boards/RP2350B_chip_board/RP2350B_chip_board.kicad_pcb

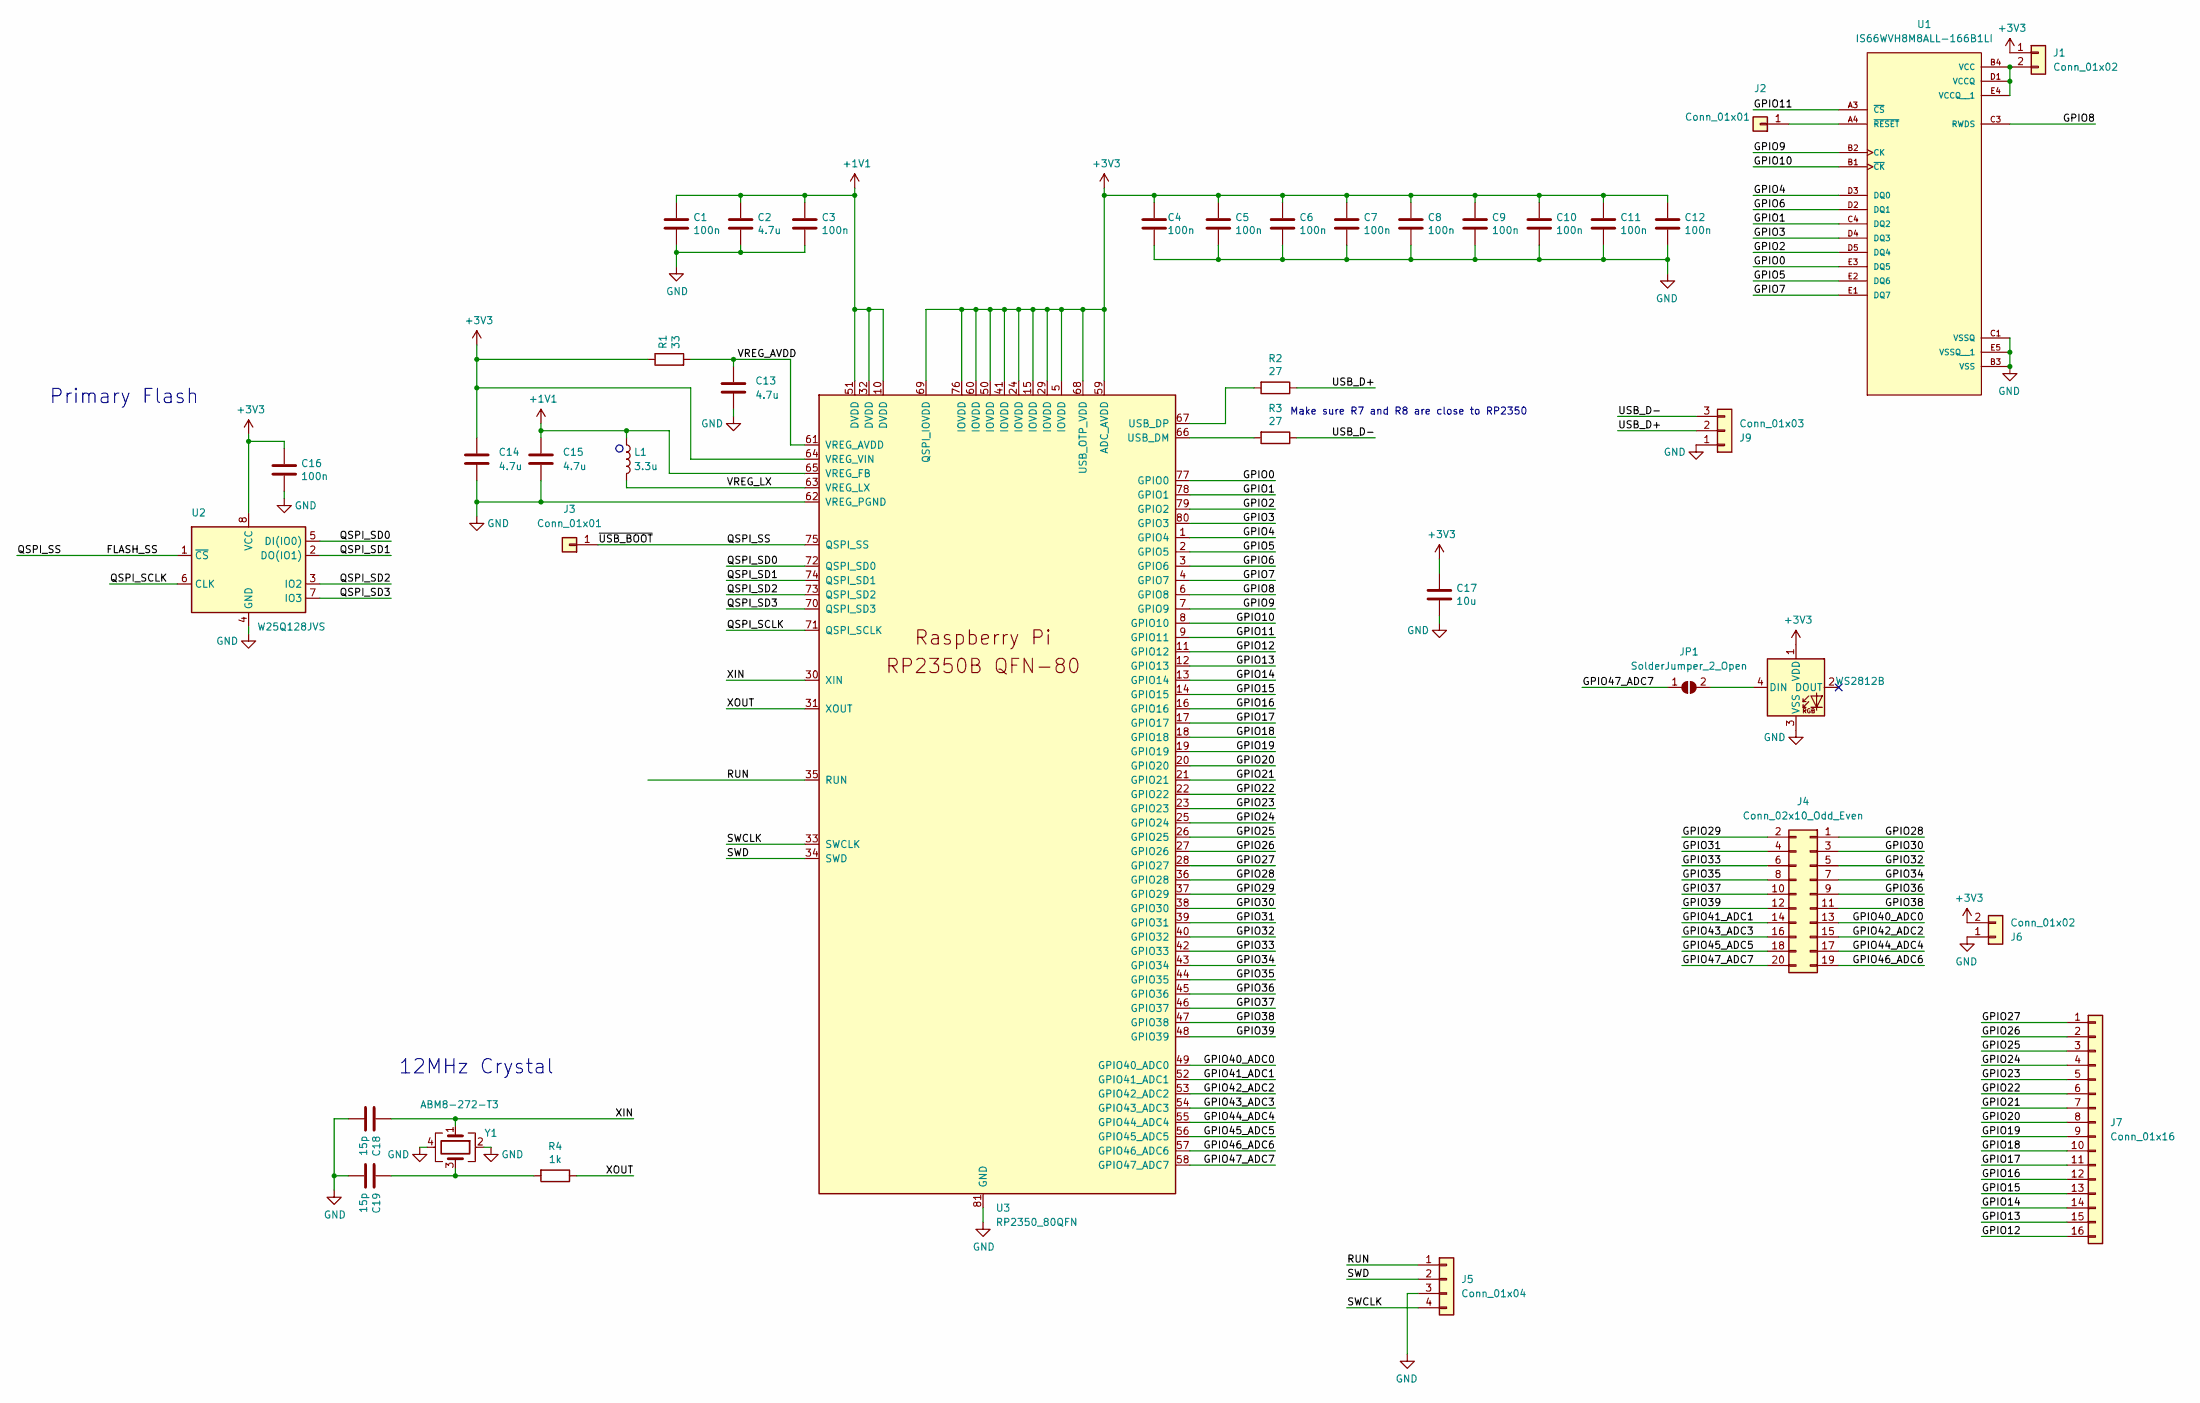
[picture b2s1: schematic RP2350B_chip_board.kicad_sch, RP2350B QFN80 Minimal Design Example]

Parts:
C1, C3, C4, C5, C6, C7, C8, C9, C10, C11, C12, C16: 100n; C_0402_1005Metric
C2, C13: 4.7u; C_0402_1005Metric
C14, C15: 4.7u; C_0402_1005Metric_small_pads
C17: 10u; C_0805_2012Metric
C18, C19: 15p; C_0402_1005Metric
D1: WS2812B; LED_WS2812B_PLCC4_5.0x5.0mm_P3.2mm
J1, J6: Conn_01x02; PinHeader_1x02_P2.00mm_Vertical
J2, J3: Conn_01x01; PinHeader_1x01_P2.00mm_Vertical
J4: Conn_02x10_Odd_Even; PinHeader_2x10_P2.00mm_Vertical
J5: Conn_01x04; PinHeader_1x04_P2.00mm_Vertical
J7: Conn_01x16; PinHeader_1x16_P2.00mm_Vertical
J9: Conn_01x03; PinHeader_1x03_P2.00mm_Vertical
JP1: SolderJumper_2_Open; SolderJumper-2_P1.3mm_Open_RoundedPad1.0x1.5mm
L1: 3.3u; L_pol_2016
R1: 33; R_0402_1005Metric
R2, R3: 27; R_0402_1005Metric
R4: 1k; R_0402_1005Metric
U1: IS66WVH8M8ALL-166B1LI; BGA25C100P5X5_800X600X120N; PARTREV B2
U2: W25Q128JVS; SOIC-8_5.23x5.23mm_P1.27mm
U3: RP2350_80QFN; RP2350-QFN-80-1EP_10x10_P0.4mm_EP3.4x3.4mm_ThermalVias
Y1: ABM8-272-T3; Crystal_SMD_3225-4Pin_3.2x2.5mm

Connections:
+1V1: C1.1, C2.1, C3.1, C15.1, L1.1, U3.10 (DVDD), U3.32 (DVDD), U3.51 (DVDD), U3.65 (VREG_FB)
+3V3: C4.1, C5.1, C6.1, C7.1, C8.1, C9.1, C10.1, C11.1, C12.1, C14.1, C16.1, C17.1, D1.1 (VDD), J1.1, J6.2, R1.1, U2.8 (VCC), U3.5 (IOVDD), U3.15 (IOVDD), U3.24 (IOVDD), U3.29 (IOVDD), U3.41 (IOVDD), U3.50 (IOVDD), U3.59 (ADC_AVDD), U3.60 (IOVDD), U3.64 (VREG_VIN), U3.68 (USB_OTP_VDD), U3.69 (QSPI_IOVDD), U3.76 (IOVDD)
/FLASH_SS: J3.1, U2.1 (~CS), U3.75 (QSPI_SS)
/GPIO0: U1.E3 (DQ5), U3.77 (GPIO0)
/GPIO1: U1.C4 (DQ2), U3.78 (GPIO1)
/GPIO2: U1.D5 (DQ4), U3.79 (GPIO2)
/GPIO3: U1.D4 (DQ3), U3.80 (GPIO3)
/GPIO4: U1.D3 (DQ0), U3.1 (GPIO4)
/GPIO5: U1.E2 (DQ6), U3.2 (GPIO5)
/GPIO6: U1.D2 (DQ1), U3.3 (GPIO6)
/GPIO7: U1.E1 (DQ7), U3.4 (GPIO7)
/GPIO8: U1.C3 (RWDS), U3.6 (GPIO8)
/GPIO9: U1.B2 (CK), U3.7 (GPIO9)
/GPIO10: U1.B1 (~CK), U3.8 (GPIO10)
/GPIO11: U1.A3 (~CS), U3.9 (GPIO11)
/GPIO12: J7.16, U3.11 (GPIO12)
/GPIO13: J7.15, U3.12 (GPIO13)
/GPIO14: J7.14, U3.13 (GPIO14)
/GPIO15: J7.13, U3.14 (GPIO15)
/GPIO16: J7.12, U3.16 (GPIO16)
/GPIO17: J7.11, U3.17 (GPIO17)
/GPIO18: J7.10, U3.18 (GPIO18)
/GPIO19: J7.9, U3.19 (GPIO19)
/GPIO20: J7.8, U3.20 (GPIO20)
/GPIO21: J7.7, U3.21 (GPIO21)
/GPIO22: J7.6, U3.22 (GPIO22)
/GPIO23: J7.5, U3.23 (GPIO23)
/GPIO24: J7.4, U3.25 (GPIO24)
/GPIO25: J7.3, U3.26 (GPIO25)
/GPIO26: J7.2, U3.27 (GPIO26)
/GPIO27: J7.1, U3.28 (GPIO27)
/GPIO28: J4.1, U3.36 (GPIO28)
/GPIO29: J4.2, U3.37 (GPIO29)
/GPIO30: J4.3, U3.38 (GPIO30)
/GPIO31: J4.4, U3.39 (GPIO31)
/GPIO32: J4.5, U3.40 (GPIO32)
/GPIO33: J4.6, U3.42 (GPIO33)
/GPIO34: J4.7, U3.43 (GPIO34)
/GPIO35: J4.8, U3.44 (GPIO35)
/GPIO36: J4.9, U3.45 (GPIO36)
/GPIO37: J4.10, U3.46 (GPIO37)
/GPIO38: J4.11, U3.47 (GPIO38)
/GPIO39: J4.12, U3.48 (GPIO39)
/GPIO40_ADC0: J4.13, U3.49 (GPIO40_ADC0)
/GPIO41_ADC1: J4.14, U3.52 (GPIO41_ADC1)
/GPIO42_ADC2: J4.15, U3.53 (GPIO42_ADC2)
/GPIO43_ADC3: J4.16, U3.54 (GPIO43_ADC3)
/GPIO44_ADC4: J4.17, U3.55 (GPIO44_ADC4)
/GPIO45_ADC5: J4.18, U3.56 (GPIO45_ADC5)
/GPIO46_ADC6: J4.19, U3.57 (GPIO46_ADC6)
/GPIO47_ADC7: J4.20, JP1.1 (A), U3.58 (GPIO47_ADC7)
/QSPI_SCLK: U2.6 (CLK), U3.71 (QSPI_SCLK)
/QSPI_SD0: U2.5 (DI(IO0)), U3.72 (QSPI_SD0)
/QSPI_SD1: U2.2 (DO(IO1)), U3.74 (QSPI_SD1)
/QSPI_SD2: U2.3 (IO2), U3.73 (QSPI_SD2)
/QSPI_SD3: U2.7 (IO3), U3.70 (QSPI_SD3)
/RUN: J5.1, U3.35 (RUN)
/SWCLK: J5.4, U3.33 (SWCLK)
/SWD: J5.2, U3.34 (SWD)
/USB_D+: J9.2, R2.1
/USB_D-: J9.3, R3.1
/VREG_AVDD: C13.1, R1.2, U3.61 (VREG_AVDD)
/VREG_LX: L1.2, U3.63 (VREG_LX)
/XIN: C18.1, U3.30 (XIN), Y1.1
/XOUT: R4.1, U3.31 (XOUT)
GND: C1.2, C2.2, C3.2, C4.2, C5.2, C6.2, C7.2, C8.2, C9.2, C10.2, C11.2, C12.2, C13.2, C14.2, C15.2, C16.2, C17.2, C18.2, C19.2, D1.3 (VSS), J5.3, J6.1, J9.1, U1.B3 (VSS), U1.C1 (VSSQ), U1.E5 (VSSQ__1), U2.4 (GND), U3.62 (VREG_PGND), U3.81 (GND), Y1.2, Y1.4
unnamed: C19.1, R4.2, Y1.3
unnamed: D1.4 (DIN), JP1.2 (B)
unnamed: J1.2, U1.B4 (VCC), U1.D1 (VCCQ), U1.E4 (VCCQ__1)
unnamed: J2.1, U1.A4 (~RESET)
unnamed: R3.2, U3.66 (USB_DM)
unnamed: R2.2, U3.67 (USB_DP)

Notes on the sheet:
12MHz Crystal
Primary Flash
Make sure R7 and R8 are close to RP2350

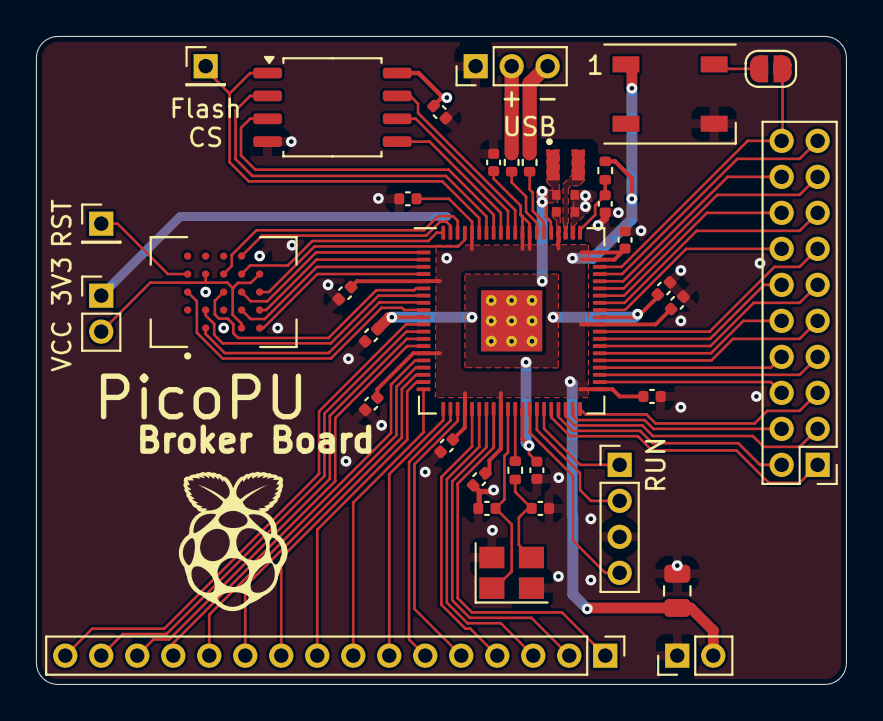
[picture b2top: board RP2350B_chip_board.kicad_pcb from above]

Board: 2 copper layers, 45.0 x 36.0 mm, 38 parts (0 on the bottom side), 72 nets.
